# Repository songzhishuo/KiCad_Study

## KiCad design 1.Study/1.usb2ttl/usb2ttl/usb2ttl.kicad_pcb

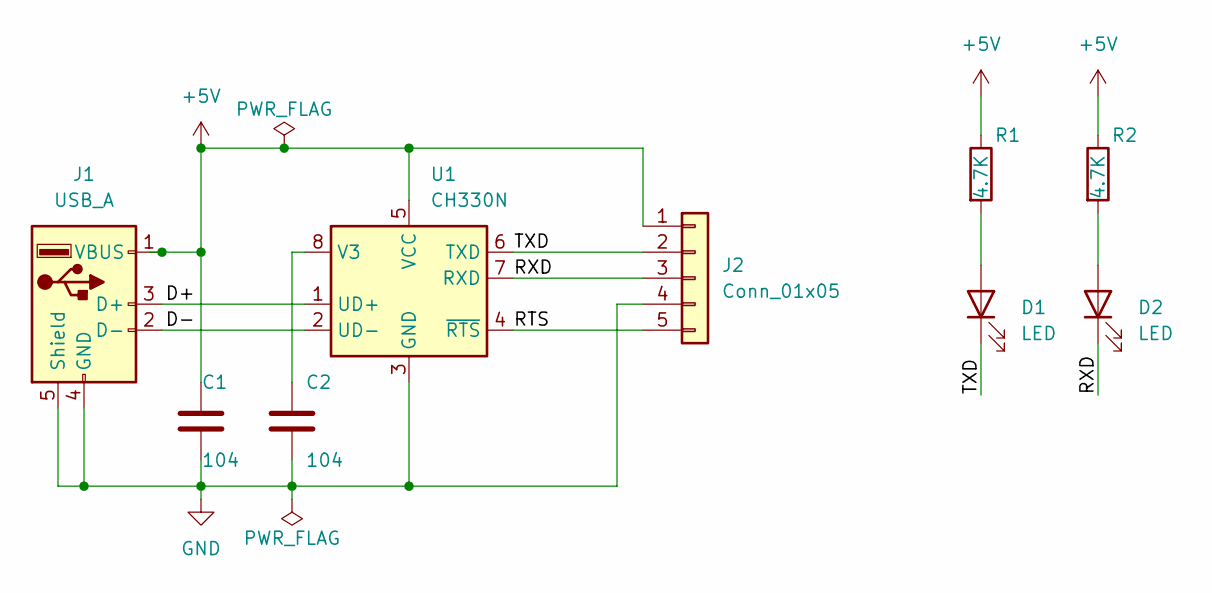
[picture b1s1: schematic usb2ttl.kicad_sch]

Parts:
C1, C2: 104; C_0603_1608Metric
D1, D2: LED; LED_0603_1608Metric
J1: USB_A; USB_A_CNCTech_1001-011-01101_Horizontal
J2: Conn_01x05; PinSocket_1x05_P2.54mm_Horizontal
R1, R2: 4.7K; R_0603_1608Metric
U1: CH330N; SOIC-8_3.9x4.9mm_P1.27mm

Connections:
+5V: C1.1, J1.1 (VBUS), J2.1, R1.1, R2.1, U1.5 (VCC)
/D+: J1.3 (D+), U1.1 (UD+)
/D-: J1.2 (D-), U1.2 (UD-)
/RTS: J2.5, U1.4 (~RTS)
/RXD: D2.1 (K), J2.3, U1.7 (RXD)
/TXD: D1.1 (K), J2.2, U1.6 (TXD)
GND: C1.2, C2.2, J1.4 (GND), J1.5 (Shield), J2.4, U1.3 (GND)
unnamed: C2.1, U1.8 (V3)
unnamed: D1.2 (A), R1.2
unnamed: D2.2 (A), R2.2

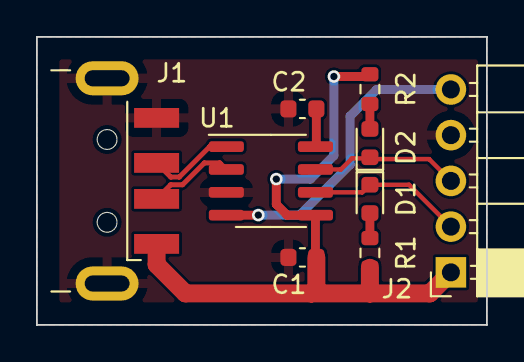
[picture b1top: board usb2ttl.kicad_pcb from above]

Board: 2 copper layers, 25.0 x 16.0 mm, 9 parts (0 on the bottom side), 10 nets.

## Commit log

2022-08-21 Add: 添加UI切换工具
2022-08-21 Add: 添加操作文档
2022-08-21 Add: 添加练习工程1 USB2ttl
